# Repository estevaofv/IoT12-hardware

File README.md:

# Status

**Experimental. Do not replicate.**

**You should be present at all times when using this circuit in case something goes wrong.**

# IoT12-hardware
Schematic and PCB files of the IoT12 solder iron temperature controller for T12 tips.

My [Kicad library](https://github.com/atoomnetmarc/ATOOMNETKICAD) is used in this project.

Control Board:\

Power Supply:\

# Checklist

:ballot_box_with_check:Design schematic\
:ballot_box_with_check:Route V1 control board PCB\
:ballot_box_with_check:Slept a few days before ordering V1 control board PCB\
:ballot_box_with_check:Order V1 control board PCB\
:ballot_box_with_check:Made my first github repository\
:ballot_box_with_check:V1 control board PCB arrived\
:ballot_box_with_check:Solder V1 control board PCB and make assembly instructions\
:ballot_box_with_check:Observe that there is something wrong in schematic\
:ballot_box_with_check:Debug V1 control board PCB\
:ballot_box_with_check:Redesign control board PCB, add microcontroller\
:ballot_box_with_check:Order V2 control board PCB\
:ballot_box_with_check:Design power supply PCB\
:ballot_box_with_check:Order power supply PCB\
:ballot_box_with_check:V2 control board PCB and power supply PCB arrived\
:ballot_box_with_check:Solder V2 control board PCB and make assembly instructions\
:ballot_box_with_check:Solder V1 power supply PCB and make assembly instructions\
:black_square_button:Debug V2 control board PCB\
:ballot_box_with_check:Start making firmware\
:black_square_button:Finish first firmware version\
:black_square_button:...\
:black_square_button:profit

# Checklist V2.0 control PCB

Worky (after bodge fix)?

:ballot_box_with_check:SAMD21 debug LED\
:ballot_box_with_check:SAMD21 USB device\
:ballot_box_with_check:SAMD21 SWD\
:ballot_box_with_check:SAMD21 TP1/D0\
:ballot_box_with_check:SAMD21 TP2/D1\
:ballot_box_with_check:SAMD21 TP3/D9\
:ballot_box_with_check:SAMD21 TP4/D10\
:ballot_box_with_check:SAMD21 HEAT_INT\
:ballot_box_with_check:SAMD21 HEAT_PWM\
:ballot_box_with_check:SAMD21 I2C minion\
:ballot_box_with_check:SAMD21 I2S_GAIN0\
:ballot_box_with_check:SAMD21 I2S_GAIN1\
:ballot_box_with_check:SAMD21 I2S_SD\
:ballot_box_with_check:SAMD21 ADC_RDY\
:ballot_box_with_check:SAMD21 I2C ADC\
:ballot_box_with_check:SAMD21 I2C ADC NTC\
:ballot_box_with_check:SAMD21 I2C ADC TEMP\
:ballot_box_with_check:SAMD21 I2C ADC VIN\
:ballot_box_with_check:SAMD21 I2C ADC IRON_CURRENT\
:ballot_box_with_check:SAMD21 I2C EEPROM\
:ballot_box_with_check:SAMD21 ADC NTC\
:ballot_box_with_check:SAMD21 ADC TEMP\
:ballot_box_with_check:SAMD21 ADC VIN\
:ballot_box_with_check:SAMD21 ADC IRON_CURRENT\
:ballot_box_with_check:SAMD21 ADC AIN_COMP\
:ballot_box_with_check:SAMD21 AC AIN_COMP\
:ballot_box_with_check:ESP32 LCD_LED\
:ballot_box_with_check:ESP32 ROT_SW\
:ballot_box_with_check:ESP32 ROT_A\
:ballot_box_with_check:ESP32 ROT_B\
:ballot_box_with_check:ESP32 I2S\
:ballot_box_with_check:ESP32 I2C\
:ballot_box_with_check:ESP32 JTAG\
:ballot_box_with_check:ESP32 LCD\
:ballot_box_with_check:ESP32 HEAT_INT

# Changelog

**Control board PCB version V2.1**

- Swapped SDA/SCL I2C minion pins on heater controller.
- Swapped SDA/SCL I2C master pins on heater controller.
- Renamed PWM_HEAT to HEAT_PWM.
- Re-added MAX809S voltage monitor to keep ESP32 in reset if 3.3V is too low.
- Changed value of R82 from 1M to 4k7.

**Control board PCB version V2.0**

- Replace safety features by microcontroller.
- Heating control now done by microcontroller.
- Changed shape and layout of pcb.

**Control board PCB version V1.1**

- Added explanation to schematic about using matched resistors for the instrumentation amplifiers.
- Changed gain resistors of the instrumentation amplifiers as to keep Vout under 1V at full scale input.
- Added series diode to output of voltage monitor.
- Lowered value of C2-C5 from 10nF to 1nF.
- Added D9 and D10.
- Changed value of R9 from 100R to 1k
- Added circuit to shutdown heating in case of overheating tip.

**Control board PCB version V1.0**

- First version that got made into PCB form.

# Eratta

**Control board PCB version V2.1**

- No known erratum.

**Control board PCB version V2.0**

- I2C to heater controller not working. SDA/SCL are swapped. Swap them on the PCB near R55 and R56 to make the ESP32 communicate to the heater controller.
- A theme is developing :unamused:. I2C from the heater controller to the I2C EEPROM and ADC is not working. SDA/SCL are swapped. Swap them between R53, R54 and the heater controller on the bottom where the SDA/SCL traces run next to each other.
- ESP32 will lockup if power supply rise time is too slow.

**Control board PCB version V1.1**

- Overheating circuit not very stable. No fix.

**Control board PCB version V1.0**

- Silkscreen error in 'Solder iron connector'-block. '5, red, +.' and '4, black, ground.' are switched resulting in negative voltages for positive temperatures. Switch leads will solve this. Corrected in next PCB version.
- Gain of instrumentation amplifiers not correct.
- Programming by USB is impossible.
- Measuring temperature takes too long (20ms).

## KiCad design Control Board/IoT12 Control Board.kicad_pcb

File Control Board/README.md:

# Assembly instructions Control Board

## Solder

Solder components in the following order.
Use the [interactive BOM](bom/ibom.html) for values and positions of the components.

### Integrated circuit

U1.
U2.
U3, U4.
U5.
U6.
U7.

### Transistor

Q1, Q2.
Q3.

### Diode

D1, D2, D3, D4, D12.
D5.
D6, D7, D8.
D9.
D10.
D11.

### Inductor

L1.
L2.

### Resistor

R1.
R10, R11, R12.
R20.
R21.
R30.
R31, R32, R33, R34.
R40.
R52.
R50, R51, R53, R54, R55, R56, R57, R58, R59, R82.
R60, R61, R62, R63. **Read schematic notes about these resistors.**
R64.
R70.
R71, R72.
R80, R81, R83, R84.

### Capacitor

C1, C2.
C10.
C20, C21, C22.
C30, C31, C32, C33, C34, C35, C36, C37, C38.
C40, C41.
C50, C60, C61.
C70, C71, C73.

### Crystal

Y1.

## Clean PCB

[Clean your printed circuit board](http://letmegooglethat.com/?q=how+to+clean+flux+after+soldering). It should be squeaky clean, no flux residue or other crud should remain.

### Switch, back of PCB

SW2.

### Connector, back of PCB

J10.

### Connector, front of PCB

A2: 2 pcs of 1x8pin 2.54mm female headers.

### Connector, back of PCB

A1: 2 pcs of 1x19pin 2.54mm female headers.
J9, J10. 2x5pin 2.54mm male headers.

### Fuse, back of PCB

## Clean PCB, again.

Yes, do it.

### Encoder, front of PCB

Solder SW1 and remove nut and washer.

### Module, front of PCB

A3. Use pin male headers. Also for SPK pins.

## Inspect

Inspect all solder joints. They should all be [nicely soldered](https://www.google.com/search?q=proper+solder+joint), no [solder bridges](https://www.google.com/search?q=picture+of+a+solder+bridge) should be present. Have a magnifying glass or (digital) microscope? Use it.

### GX12-5 connector

Solder some wires between a GX12-5 socket connector and the back of the pcb. On the back of the pcb there are a few pads labeled 1 to 5, solder them to pin 1 to 5 on the GX12-5 connector.

| Pin#  | Wire color    | Description   |
| --:   | --            | --            |
| 1     | blue          | shake         |
| 2     | white         | NTC           |
| 3     | green         | ESD           |
| 4     | black         | T12-          |
| 5     | red           | T12+          |

## Testing

Connect a (KSGER) T12 solder iron handle with the T12 tip firmly seated inside.

- Measure about 1MΩ between the tip of the iron and EARTH hole at the Power supply connection on the PCB.
- Now measure some values at the solder iron connector holes.\
The heater resistor between 4 (black) and 5 (red): 8Ω
- Switch over to measure mV. When you have not touched the handle and tip for half an hour you should read 0mV. Grab the tip with your hand. You should notice an increasing voltage, possibly a rise until 0.1mV. It is possible your voltmeter is not capable of measuring in the microvolt range. You can heat the tip with a flame for a few seconds to increase the voltage some more.
- The NTC between 4 (black) and 2 (white): 5KΩ@22°C, but that could vary slightly when not measuring at the same room temperature.
- Test the tilt sensor. Point iron up and measure between 1 (blue) and 3 (green): >2MΩ\
Point iron down and measure a low resistance: <100Ω

Solder a red wire to 24V and black wire to GND of the power supply connector holes, both on the back.\
Slowly increase power supply until 10V with max 50mA power. Measure voltage at C71. You should measure 5V. The current draw should be under 10mA.

Switch off power supply and mount the LCD display module and the ESP32 module.

Increase maximum power supply current to 250mA. Instantly increase voltage to 5V, the slowly to 10V, current should not exceed 150mA. When at 10V the current draw should be under 100mA.
You may increase voltage to 24V, consumed power should be under 40mA.

When all tests went well, start writing your own firmware. Or [flash my firmware](https://github.com/atoomnetmarc/IoT12-firmware) when it becomes available.\
Projected firmware availability date: soon™

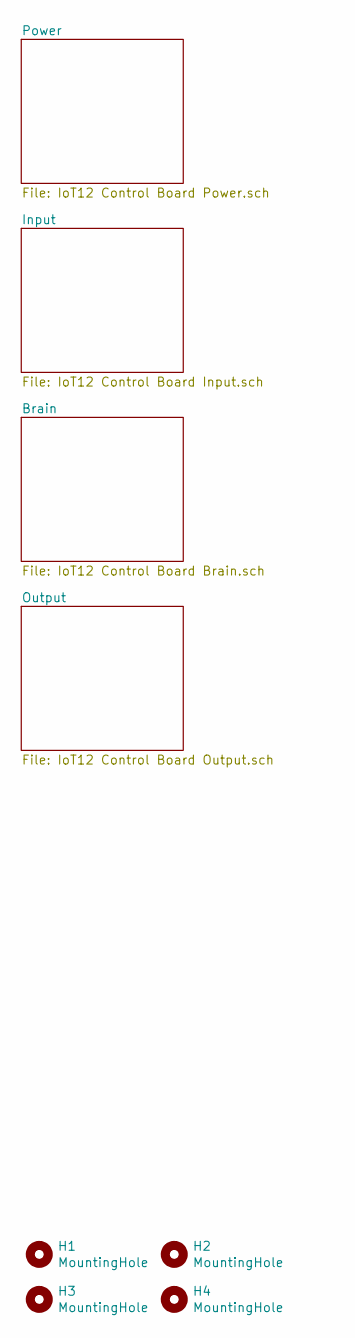
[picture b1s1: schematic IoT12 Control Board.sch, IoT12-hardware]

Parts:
H1, H2, H3, H4: MountingHole; MountingHole_3.2mm_M3_Pad_Via

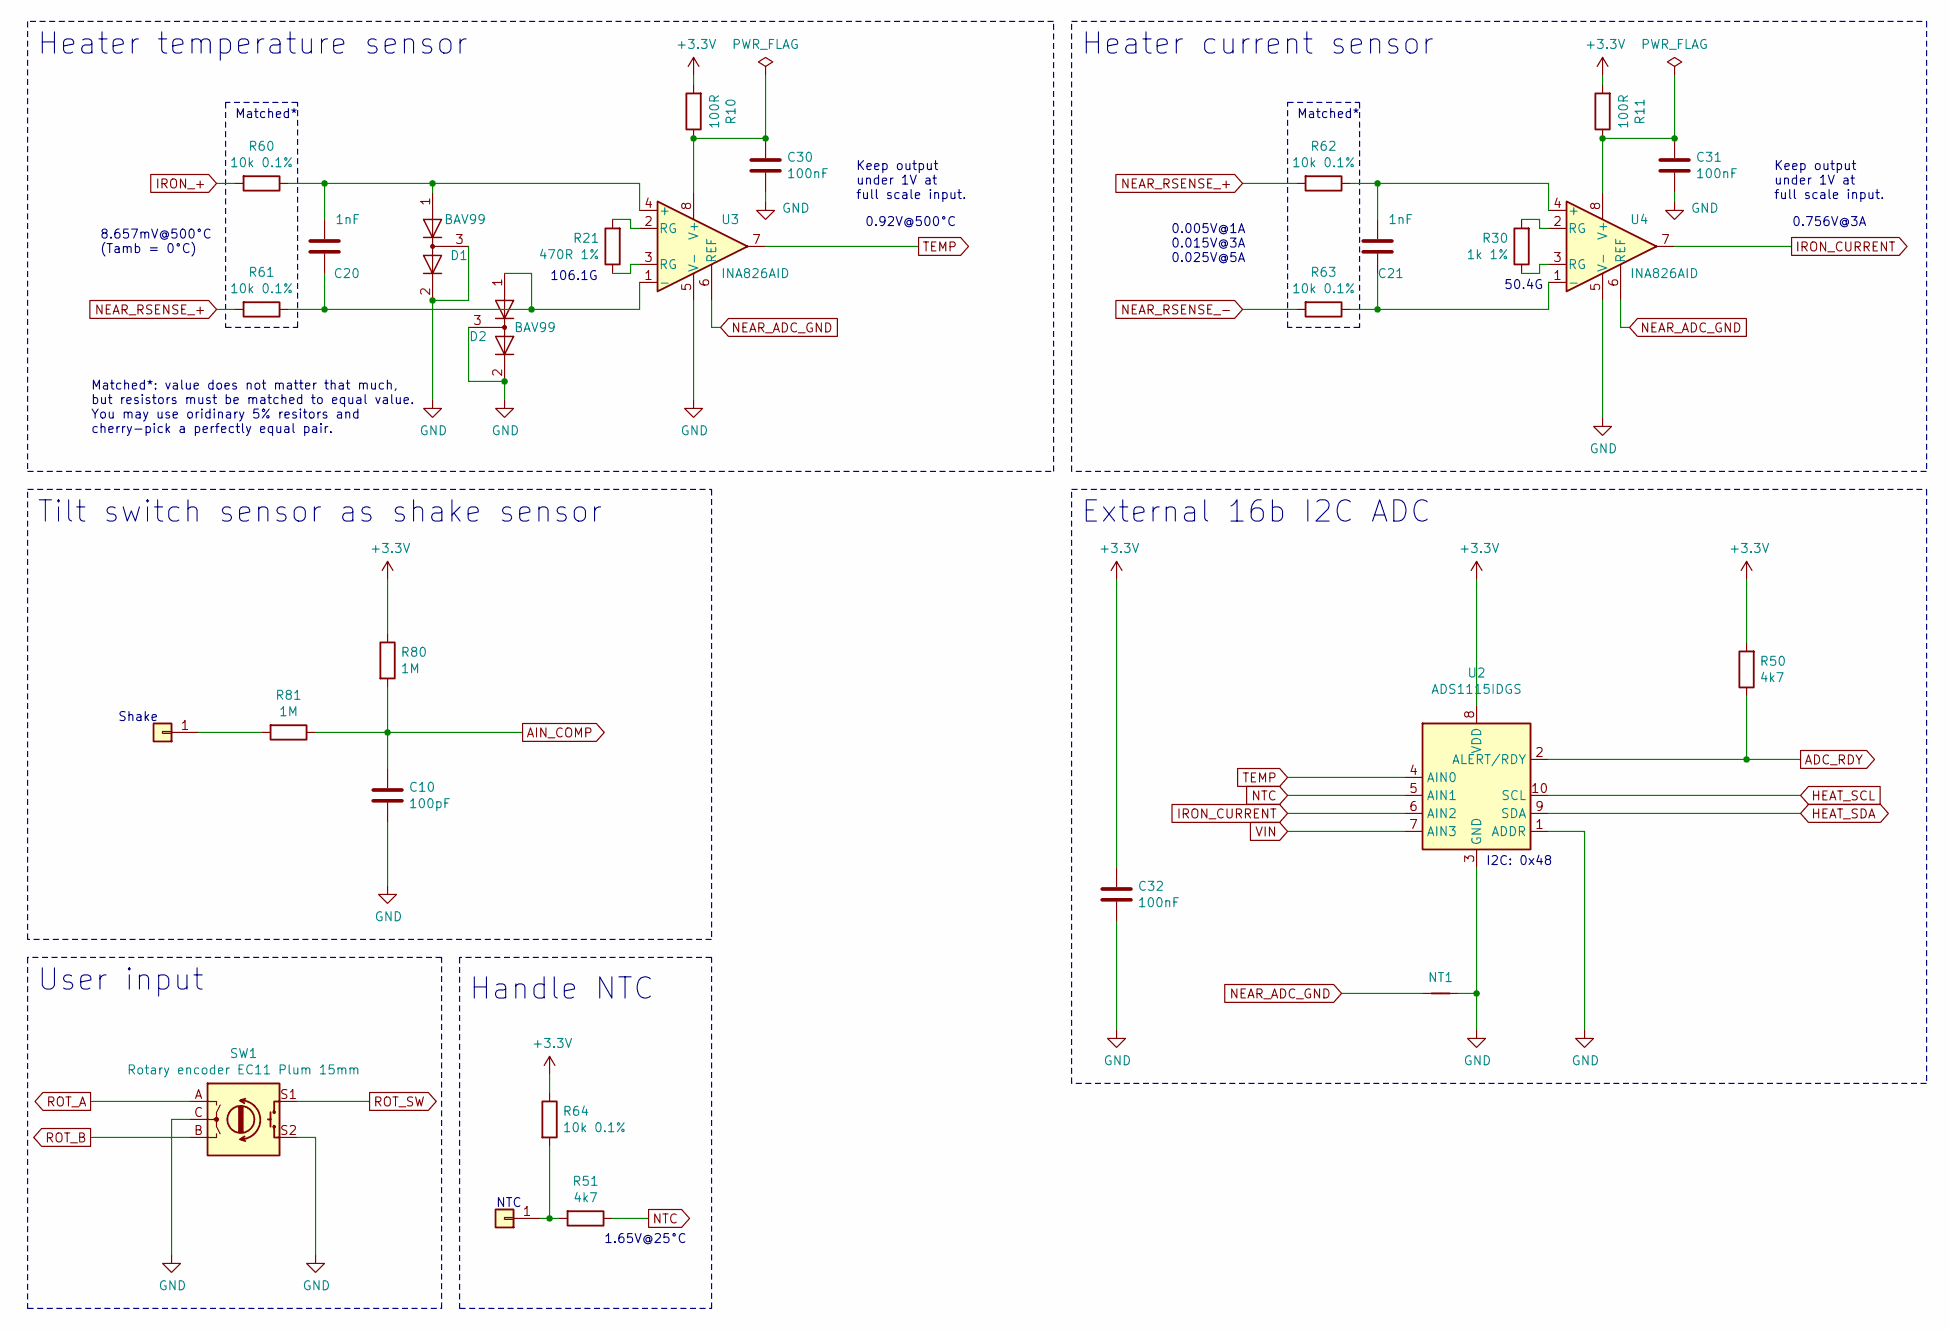
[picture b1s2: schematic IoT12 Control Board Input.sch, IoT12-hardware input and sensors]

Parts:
C10: 100pF; C_0805_2012Metric_Pad1.18x1.45mm_HandSolder
C20, C21: 1nF; C_0805_2012Metric_Pad1.18x1.45mm_HandSolder
C30, C31, C32: 100nF; C_0805_2012Metric_Pad1.18x1.45mm_HandSolder
D1, D2: BAV99; SOT-23
J1, J2: TestPoint_THTPad_D2.0mm_Drill1.0mm
NT1: NetTie-2_SMD_Pad0.25mm
R10, R11: 100R; R_0805_2012Metric_Pad1.20x1.40mm_HandSolder
R21: 470R 1%; R_0805_2012Metric_Pad1.20x1.40mm_HandSolder
R30: 1k 1%; R_0805_2012Metric_Pad1.20x1.40mm_HandSolder
R50, R51: 4k7; R_0805_2012Metric_Pad1.20x1.40mm_HandSolder
R60, R61, R62, R63, R64: 10k 0.1%; R_0805_2012Metric_Pad1.20x1.40mm_HandSolder
R80, R81: 1M; R_0805_2012Metric_Pad1.20x1.40mm_HandSolder
SW1: Rotary encoder EC11 Plum 15mm; RotaryEncoder_Alps_EC11E-Switch_Vertical_H20mm_CircularMoun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
U2: ADS1115IDGS; TSSOP-10_3x3mm_P0.5mm
U3, U4: INA826AID; SOIC-8_3.9x4.9mm_P1.27mm

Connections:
ADC_RDY: R50.1, U2.2 (ALERT/RDY); also elsewhere on the board
AIN_COMP: C10.1, R80.2, R81.1; also elsewhere on the board
GND: C10.2, C30.2, C31.2, C32.2, D1.2 (A), D1.3 (K), D2.2 (A), D2.3 (K), NT1.2, SW1.C, SW1.S2, U2.1 (ADDR), U2.3 (GND), U3.5 (V-), U4.5 (V-); also elsewhere on the board
HEAT_SCL: U2.10 (SCL); also elsewhere on the board
HEAT_SDA: U2.9 (SDA); also elsewhere on the board
IRON_+: R60.2; also elsewhere on the board
IRON_CURRENT: U2.6 (AIN2), U4.7; also elsewhere on the board
NEAR_ADC_GND: NT1.1, U3.6 (REF), U4.6 (REF)
NEAR_RSENSE_+: R61.2, R62.2; also elsewhere on the board
NEAR_RSENSE_-: R63.2; also elsewhere on the board
NTC: R51.1, U2.5 (AIN1); also elsewhere on the board
unnamed: C20.1, D1.1 (K), R60.1, U3.4 (+)
unnamed: C20.2, D2.1 (K), R61.1, U3.1 (-)
unnamed: C21.1, R62.1, U4.4 (+)
unnamed: C21.2, R63.1, U4.1 (-)
unnamed: C30.1, R10.1, U3.8 (V+)
unnamed: C31.1, R11.1, U4.8 (V+)
unnamed: J1.1, R81.2
unnamed: J2.1, R51.2, R64.2
unnamed: R21.1, U3.3 (RG)
unnamed: R21.2, U3.2 (RG)
unnamed: R30.1, U4.3 (RG)
unnamed: R30.2, U4.2 (RG)
ROT_A: SW1.A; also elsewhere on the board
ROT_SW: SW1.S1; also elsewhere on the board
TEMP: U2.4 (AIN0), U3.7; also elsewhere on the board
VIN: U2.7 (AIN3); also elsewhere on the board

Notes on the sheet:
User input
Heater temperature sensor
Heater current sensor
Handle NTC
NTC
Shake
Tilt switch sensor as shake sensor
50.4G
Matched*
0.005V@1A 0.015V@3A 0.025V@5A
106.1G
8.657mV@500°C (Tamb = 0°C)
0.92V@500°C
1.65V@25°C
Matched*: value does not matter that much, but resistors must be matched to equal value. You may use oridinary 5% resitors and cherry-pick a perfectly equal pair.
Keep output under 1V at full scale input.
0.756V@3A
External 16b I2C ADC
I2C: 0x48

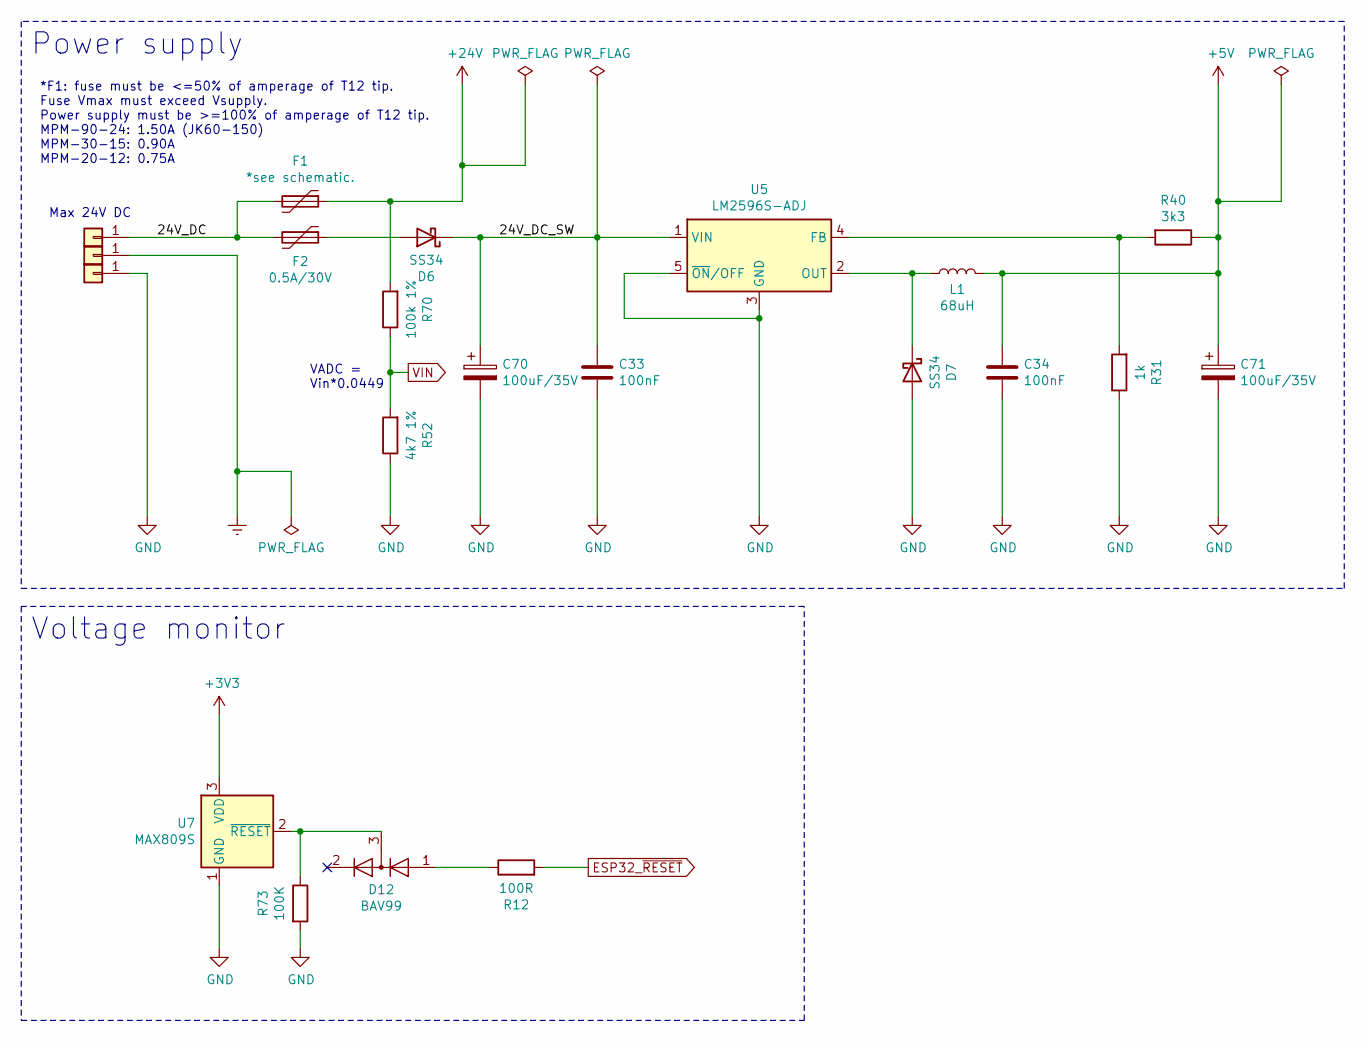
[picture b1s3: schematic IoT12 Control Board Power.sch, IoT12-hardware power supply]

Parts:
C33, C34: 100nF; C_0805_2012Metric_Pad1.18x1.45mm_HandSolder
C70, C71: 100uF/35V; CP_Elec_6.3x7.7
D6, D7: SS34; D_SMA
D12: BAV99; SOT-23
F1: *see schematic.; Fuse_Bourns_MF-RG1000
F2: 0.5A/30V; Fuse_Bourns_MF-RG400
J6, J7, J8: TestPoint_THTPad_D2.0mm_Drill1.0mm
L1: 68uH; L_12x12mm_H8mm
R12: 100R; R_0805_2012Metric_Pad1.20x1.40mm_HandSolder
R31: 1k; R_0805_2012Metric_Pad1.20x1.40mm_HandSolder
R40: 3k3; R_0805_2012Metric_Pad1.20x1.40mm_HandSolder
R52: 4k7 1%; R_0805_2012Metric_Pad1.20x1.40mm_HandSolder
R70: 100k 1%; R_0805_2012Metric_Pad1.20x1.40mm_HandSolder
R73: 100K; R_0805_2012Metric_Pad1.20x1.40mm_HandSolder
U5: LM2596S-ADJ; TO-263-5_TabPin3
U7: MAX809S; SOT-23

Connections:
+5V: C34.1, C71.1, L1.2, R40.1; also elsewhere on the board
+24V: F1.1, R70.2; also elsewhere on the board
/Power/24V_DC: F1.2, F2.2, J6.1
/Power/24V_DC_SW: C33.1, C70.1, D6.1 (K), U5.1 (VIN)
ESP32_~RESET: R12.2; also elsewhere on the board
Earth: J7.1; also elsewhere on the board
GND: C33.2, C34.2, C70.2, C71.2, D7.2 (A), J8.1, R31.1, R52.1, R73.2, U5.3 (GND), U5.5 (~ON~/OFF), U7.1 (GND); also elsewhere on the board
unnamed: D6.2 (A), F2.1
unnamed: D7.1 (K), L1.1, U5.2 (OUT)
unnamed: D12.1 (K), R12.1
unnamed: D12.3 (K), R73.1, U7.2 (~RESET)
unnamed: R31.2, R40.2, U5.4 (FB)
VIN: R52.2, R70.1; also elsewhere on the board

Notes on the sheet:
Power supply
VADC = Vin*0.0449
Max 24V DC
Voltage monitor
*F1: fuse must be <=50% of amperage of T12 tip. Fuse Vmax must exceed Vsupply. Power supply must be >=100% of amperage of T12 tip. MPM-90-24: 1.50A (JK60-150) MPM-30-15: 0.90A MPM-20-12: 0.75A

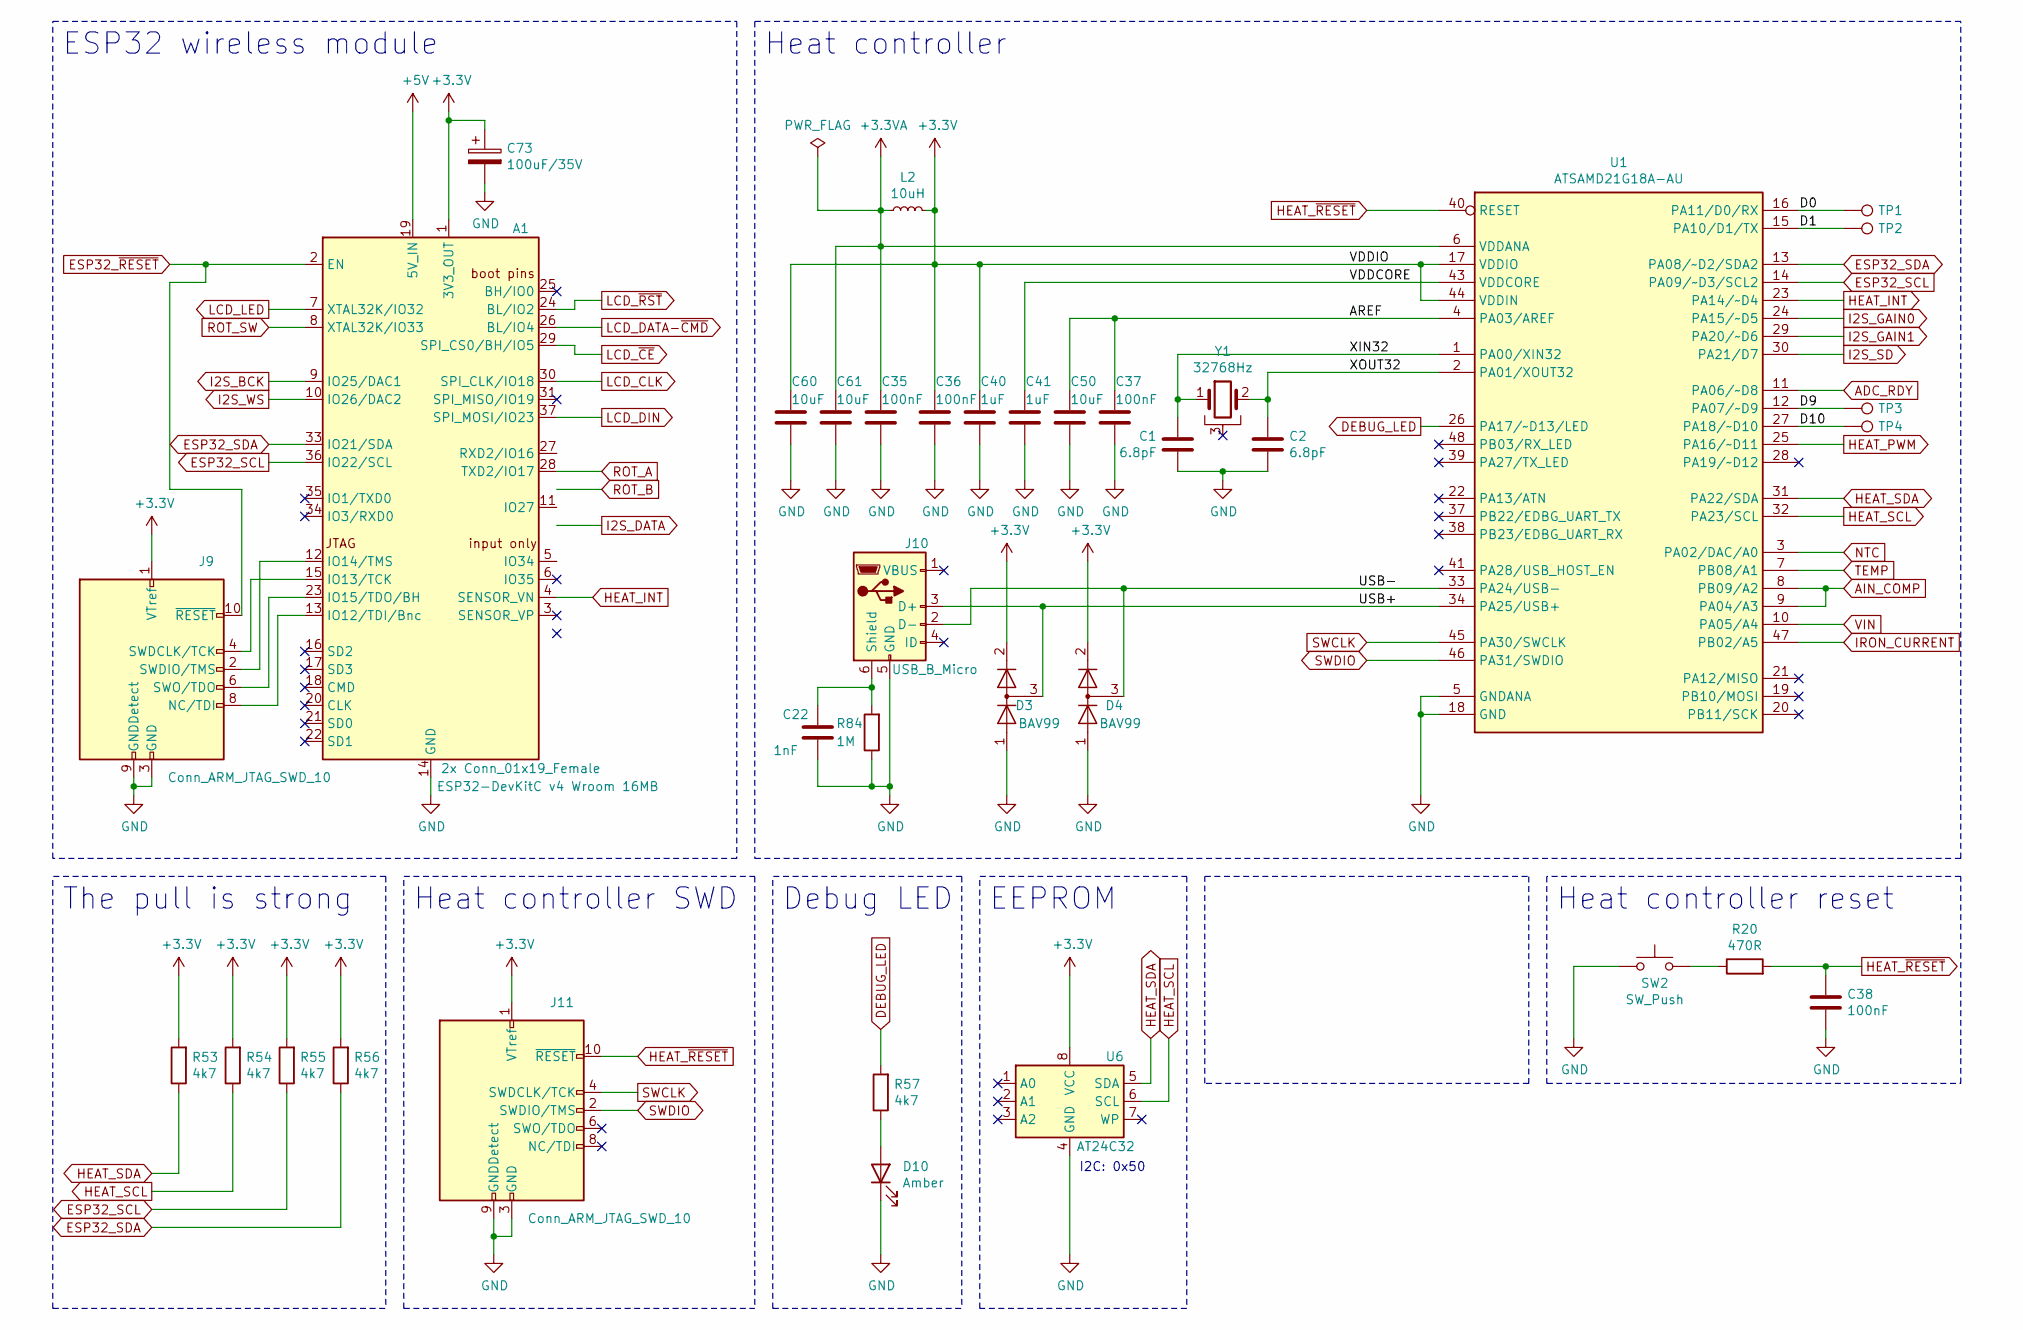
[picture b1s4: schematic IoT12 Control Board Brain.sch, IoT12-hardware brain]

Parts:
A1: 2x Conn_01x19_Female; ESP32-DevKitC
C1, C2: 6.8pF; C_0805_2012Metric_Pad1.18x1.45mm_HandSolder
C22: 1nF; C_0805_2012Metric_Pad1.18x1.45mm_HandSolder
C35, C36, C37, C38: 100nF; C_0805_2012Metric_Pad1.18x1.45mm_HandSolder
C40, C41: 1uF; C_0805_2012Metric_Pad1.18x1.45mm_HandSolder
C50, C60, C61: 10uF; C_0805_2012Metric_Pad1.18x1.45mm_HandSolder
C73: 100uF/35V; CP_Elec_6.3x7.7
D3, D4: BAV99; SOT-23
D10: Amber; LED_0805_2012Metric_Pad1.15x1.40mm_HandSolder
J9, J11: Conn_ARM_JTAG_SWD_10; PinHeader_2x05_P2.54mm_Vertical
J10: USB_B_Micro; USB_Micro-B_Amphenol_10118194_Horizontal
L2: 10uH; L_0805_2012Metric_Pad1.15x1.40mm_HandSolder
R20: 470R; R_0805_2012Metric_Pad1.20x1.40mm_HandSolder
R53, R54, R55, R56, R57: 4k7; R_0805_2012Metric_Pad1.20x1.40mm_HandSolder
R84: 1M; R_0805_2012Metric_Pad1.20x1.40mm_HandSolder
SW2: SW_Push; SW_SPST_CK_RS282G05A3
TP1, TP2, TP3, TP4: TestPoint; TestPoint_Pad_D0.75mm
U1: ATSAMD21G18A-AU; TQFP-48_7x7mm_P0.5mm
U6: AT24C32; SOIC-8_3.9x4.9mm_P1.27mm
Y1: 32768Hz; Crystal_C26-LF_D2.1mm_L6.5mm_Horizontal_1EP_style1

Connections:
+3.3VA: C35.1, C61.1, L2.1, U1.6 (VDDANA)
+5V: A1.19 (5V_IN); also elsewhere on the board
/Brain/AREF: C37.1, C50.1, U1.4 (PA03/AREF)
/Brain/D0: TP1.1, U1.16 (PA11/D0/RX)
/Brain/D1: TP2.1, U1.15 (PA10/D1/TX)
/Brain/D9: TP3.1, U1.12 (PA07/~~D9)
/Brain/D10: TP4.1, U1.27 (PA18/~~D10)
/Brain/USB+: D3.3 (K), J10.3 (D+), U1.34 (PA25/USB+)
/Brain/USB-: D4.3 (K), J10.2 (D-), U1.33 (PA24/USB-)
/Brain/VDDCORE: C41.1, U1.43 (VDDCORE)
/Brain/XIN32: C1.1, U1.1 (PA00/XIN32), Y1.1
/Brain/XOUT32: C2.1, U1.2 (PA01/XOUT32), Y1.2
ADC_RDY: U1.11 (PA06/~~D8); also elsewhere on the board
AIN_COMP: U1.8 (PB09/A2), U1.9 (PA04/A3); also elsewhere on the board
DEBUG_LED: R57.2, U1.26 (PA17/~~D13/LED)
ESP32_SCL: A1.36 (IO22/SCL), R55.1, U1.14 (PA09/~~D3/SCL2)
ESP32_SDA: A1.33 (IO21/SDA), R56.1, U1.13 (PA08/~~D2/SDA2)
ESP32_~RESET: A1.2 (EN), J9.10 (~RESET~); also elsewhere on the board
GND: A1.14 (GND), A1.32 (GND), A1.38 (GND), C1.2, C2.2, C22.2, C35.2, C36.2, C37.2, C38.2, C40.2, C41.2, C50.2, C60.2, C61.2, C73.2, D3.1 (K), D4.1 (K), D10.1 (K), J9.3 (GND), J9.5 (GND), J9.9 (GNDDetect), J10.5 (GND), J11.3 (GND), J11.5 (GND), J11.9 (GNDDetect), R84.1, SW2.1, U1.5 (GNDANA), U1.18 (GND), U1.35 (GND), U1.42 (GND), U6.4 (GND); also elsewhere on the board
HEAT_PWM: U1.25 (PA16/~~D11); also elsewhere on the board
HEAT_SCL: R54.1, U1.32 (PA23/SCL), U6.6 (SCL); also elsewhere on the board
HEAT_SDA: R53.1, U1.31 (PA22/SDA), U6.5 (SDA); also elsewhere on the board
HEAT_~RESET: C38.1, J11.10 (~RESET~), R20.2, U1.40 (RESET)
I2S_BCK: A1.9 (IO25/DAC1); also elsewhere on the board
I2S_DATA: A1.11 (IO27); also elsewhere on the board
I2S_GAIN0: U1.24 (PA15/~~D5); also elsewhere on the board
I2S_GAIN1: U1.29 (PA20/~~D6); also elsewhere on the board
I2S_SD: U1.30 (PA21/D7); also elsewhere on the board
I2S_WS: A1.10 (IO26/DAC2); also elsewhere on the board
IRON_CURRENT: U1.47 (PB02/A5); also elsewhere on the board
LCD_CLK: A1.30 (SPI_CLK/IO18); also elsewhere on the board
LCD_DATA-~CMD: A1.26 (BL/IO4); also elsewhere on the board
LCD_DIN: A1.37 (SPI_MOSI/IO23); also elsewhere on the board
LCD_LED: A1.7 (XTAL32K/IO32); also elsewhere on the board
LCD_~CE: A1.29 (SPI_CS0/BH/IO5); also elsewhere on the board
LCD_~RST: A1.24 (BL/IO2); also elsewhere on the board
NTC: U1.3 (PA02/DAC/A0); also elsewhere on the board
unnamed: A1.12 (IO14/TMS), J9.2 (SWDIO/TMS)
unnamed: A1.13 (IO12/TDI/Bnc), J9.8 (NC/TDI)
unnamed: A1.15 (IO13/TCK), J9.4 (SWDCLK/TCK)
unnamed: A1.23 (IO15/TDO/BH), J9.6 (SWO/TDO)
unnamed: C22.1, J10.6 (Shield), R84.2
unnamed: D10.2 (A), R57.1
unnamed: R20.1, SW2.2
ROT_A: A1.27 (RXD2/IO16); also elsewhere on the board
ROT_SW: A1.8 (XTAL32K/IO33); also elsewhere on the board
SWCLK: J11.4 (SWDCLK/TCK), U1.45 (PA30/SWCLK)
SWDIO: J11.2 (SWDIO/TMS), U1.46 (PA31/SWDIO)
TEMP: U1.7 (PB08/A1); also elsewhere on the board
VIN: U1.10 (PA05/A4); also elsewhere on the board

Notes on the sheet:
ESP32 wireless module
Heat controller
Heat controller SWD
Heat controller reset
Debug LED
The pull is strong
EEPROM
I2C: 0x50

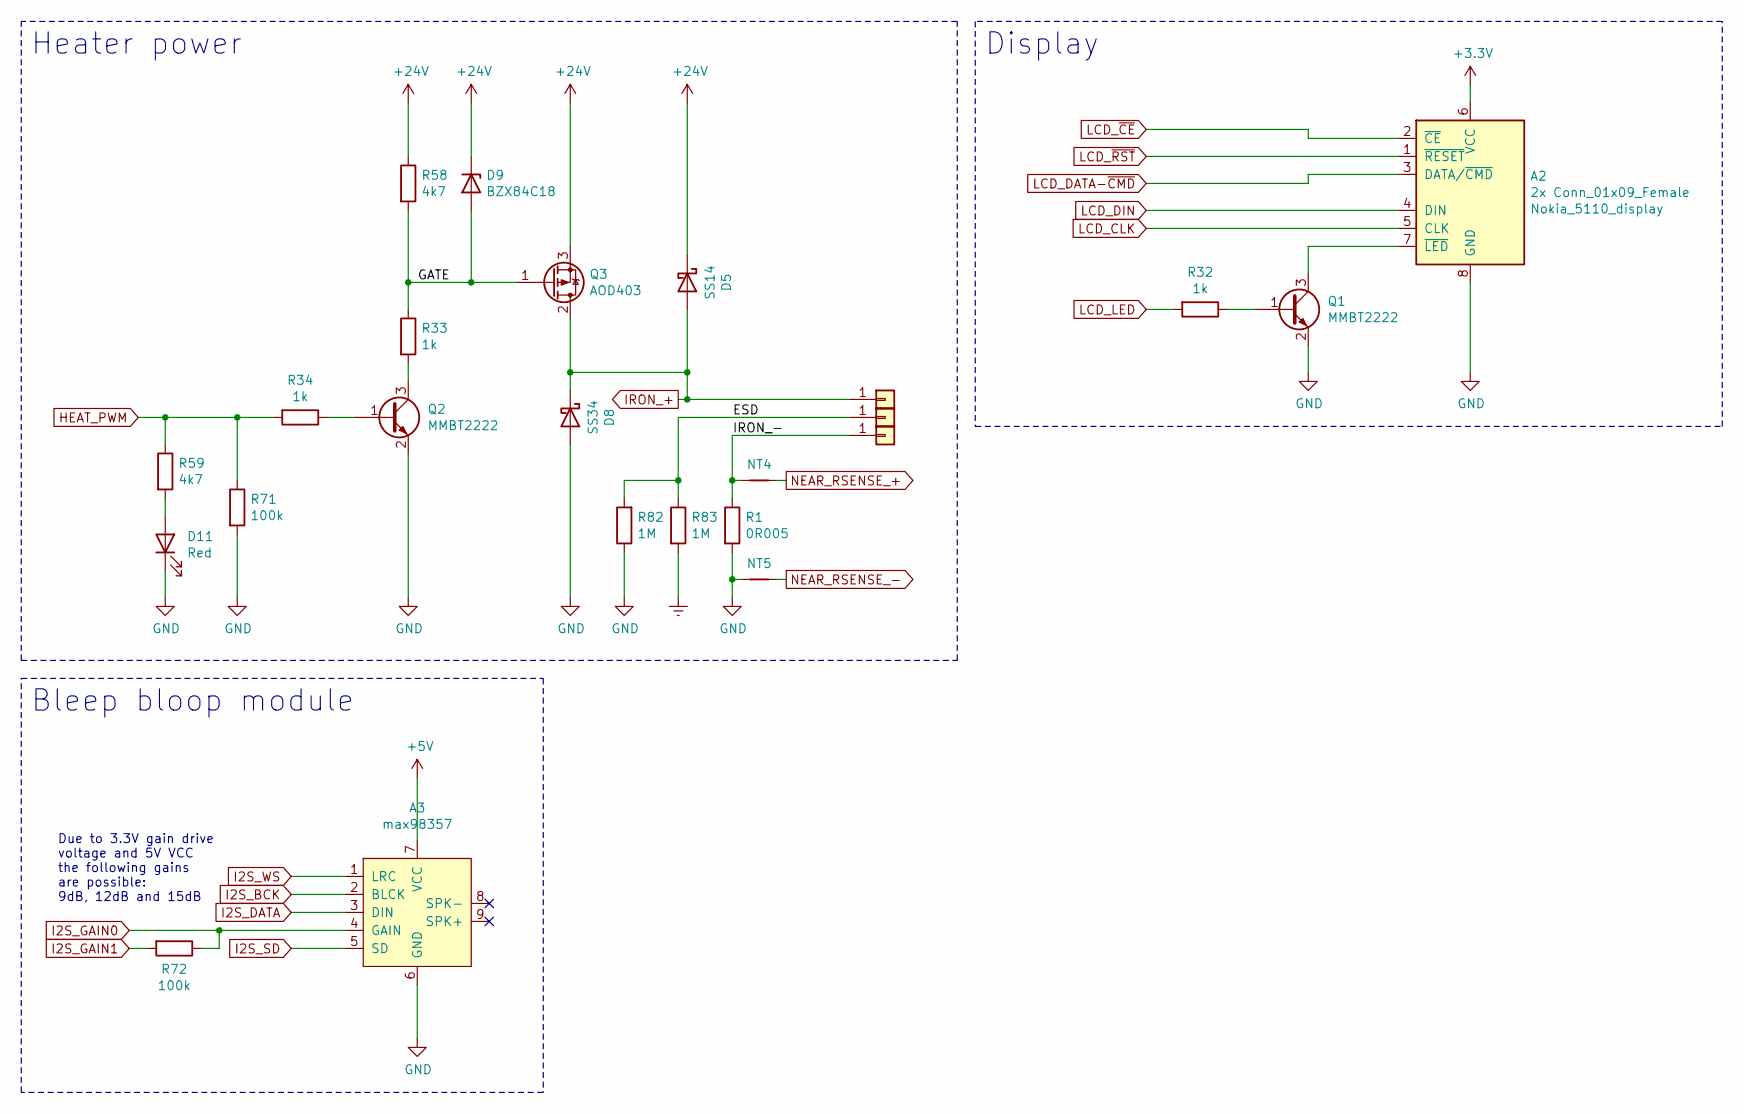
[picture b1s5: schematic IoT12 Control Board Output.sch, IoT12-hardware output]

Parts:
A2: 2x Conn_01x09_Female; Nokia_5110_display_module
A3: max98357
D5: SS14; D_SMA
D8: SS34; D_SMA
D9: BZX84C18; D_SOT-23_ANK
D11: Red; LED_0805_2012Metric_Pad1.15x1.40mm_HandSolder
J3, J4, J5: TestPoint_THTPad_D2.0mm_Drill1.0mm
NT4, NT5: NetTie-2_SMD_Pad0.25mm
Q1, Q2: MMBT2222; SOT-23
Q3: AOD403; TO-252-2
R1: 0R005; R_2512_6332Metric_Pad1.52x3.35mm_HandSolder
R32, R33, R34: 1k; R_0805_2012Metric_Pad1.20x1.40mm_HandSolder
R58, R59: 4k7; R_0805_2012Metric_Pad1.20x1.40mm_HandSolder
R71, R72: 100k; R_0805_2012Metric_Pad1.20x1.40mm_HandSolder
R82, R83: 1M; R_0805_2012Metric_Pad1.20x1.40mm_HandSolder

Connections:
+5V: A3.7 (VCC); also elsewhere on the board
+24V: D5.1 (K), D9.1 (K), Q3.3 (S), R58.1; also elsewhere on the board
/Output/ESD: J3.1, R82.2, R83.1
/Output/GATE: D9.2 (A), Q3.1 (G), R33.1, R58.2
/Output/IRON_-: J4.1, NT4.1, R1.1
Earth: R83.2; also elsewhere on the board
GND: A2.8 (GND), A3.6 (GND), D8.2 (A), D11.1 (K), NT5.1, Q1.2 (E), Q2.2 (E), R1.2, R71.2, R82.1; also elsewhere on the board
HEAT_PWM: R34.2, R59.1, R71.1; also elsewhere on the board
I2S_BCK: A3.2 (BLCK); also elsewhere on the board
I2S_DATA: A3.3 (DIN); also elsewhere on the board
I2S_GAIN0: A3.4 (GAIN), R72.1; also elsewhere on the board
I2S_GAIN1: R72.2; also elsewhere on the board
I2S_SD: A3.5 (SD); also elsewhere on the board
I2S_WS: A3.1 (LRC); also elsewhere on the board
IRON_+: D5.2 (A), D8.1 (K), J5.1, Q3.2 (D); also elsewhere on the board
LCD_CLK: A2.5 (CLK); also elsewhere on the board
LCD_DATA-~CMD: A2.3 (DATA/~CMD); also elsewhere on the board
LCD_DIN: A2.4 (DIN); also elsewhere on the board
LCD_LED: R32.2; also elsewhere on the board
LCD_~CE: A2.2 (~CE); also elsewhere on the board
LCD_~RST: A2.1 (~RESET); also elsewhere on the board
NEAR_RSENSE_+: NT4.2; also elsewhere on the board
NEAR_RSENSE_-: NT5.2; also elsewhere on the board
unnamed: A2.7 (~LED), Q1.3 (C)
unnamed: D11.2 (A), R59.2
unnamed: Q1.1 (B), R32.1
unnamed: Q2.1 (B), R34.1
unnamed: Q2.3 (C), R33.2

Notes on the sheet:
Display
Heater power
Bleep bloop module
Due to 3.3V gain drive voltage and 5V VCC the following gains are possible: 9dB, 12dB and 15dB

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
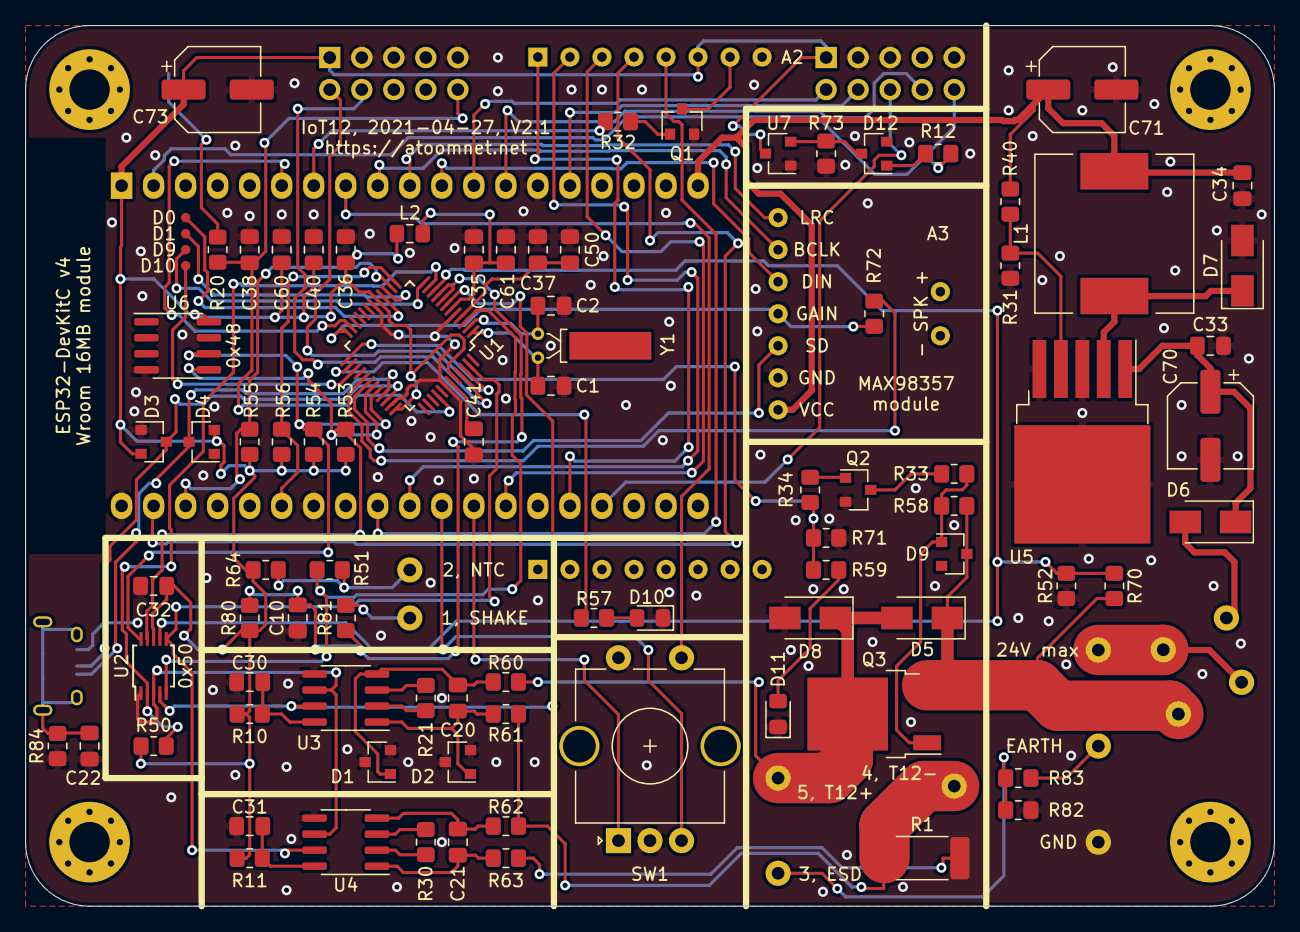
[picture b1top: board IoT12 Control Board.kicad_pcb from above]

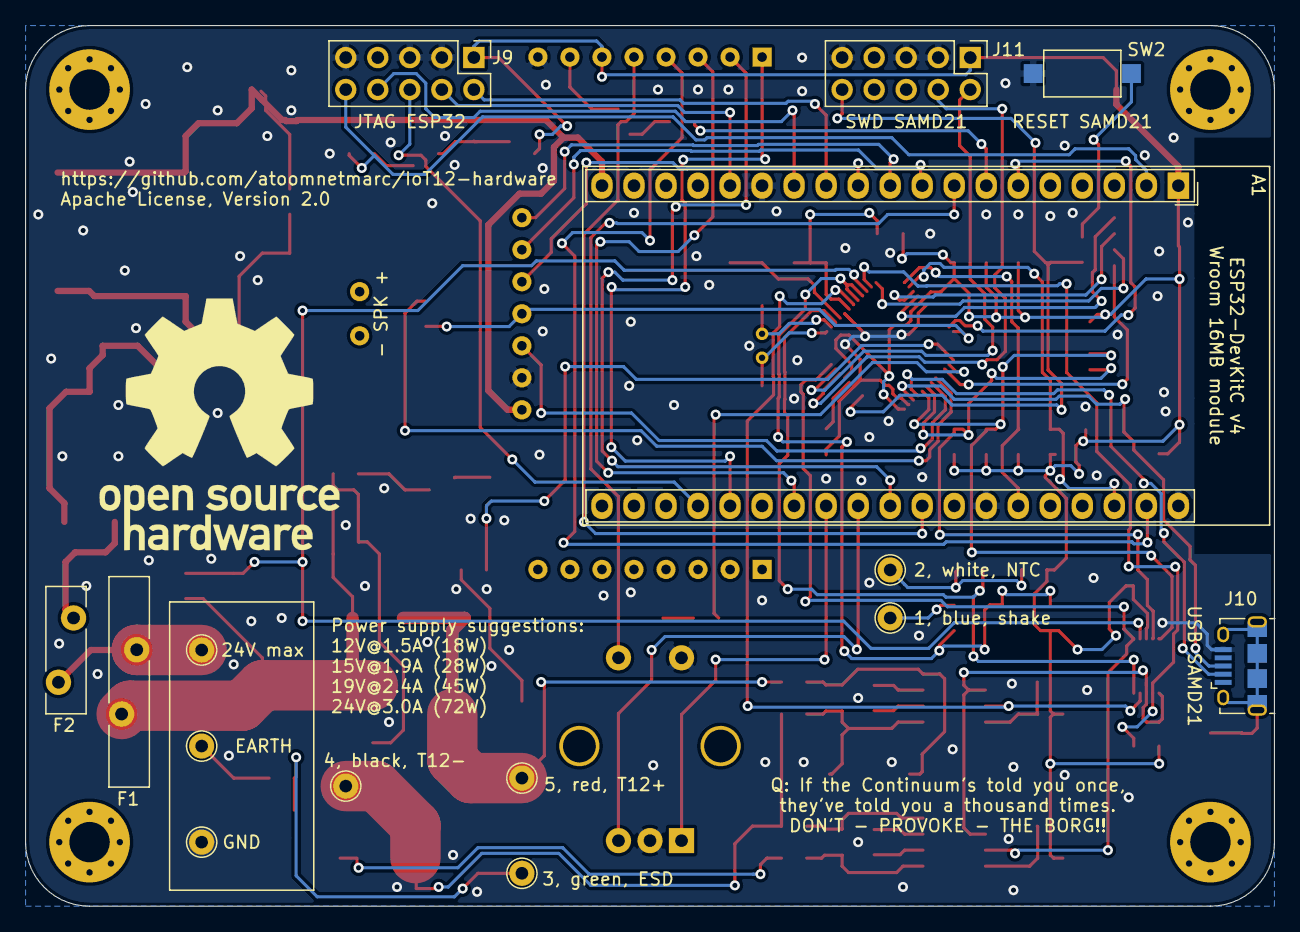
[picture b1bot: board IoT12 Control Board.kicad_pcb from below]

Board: 2 copper layers, 99.1 x 69.8 mm, 113 parts (15 on the bottom side), 86 nets.

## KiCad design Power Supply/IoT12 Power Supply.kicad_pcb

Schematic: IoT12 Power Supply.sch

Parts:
D2: Green; LED_0805_2012Metric_Pad1.15x1.40mm_HandSolder
H1, H2, H3, H4: MountingHole; MountingHole_3.2mm_M3_Pad_Via
J1, J2: Screw_Terminal_01x03; TerminalBlock_bornier-3_P5.08mm
PS1: MPM-90-24; Converter_ACDC_MeanWell_MPM-90-xx_THT
PS2: MPM-30-15*; Converter_ACDC_MeanWell_MPM-30-xx_THT
PS3: MPM-20-12*; Converter_ACDC_MeanWell_MPM-20-xx_THT
R2: 4K7; R_0805_2012Metric_Pad1.20x1.40mm_HandSolder

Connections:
/L: J1.3, PS1.1, PS2.1, PS3.1
/N: J1.2, PS1.2, PS2.2, PS3.2
/Vout+: J2.3, PS1.3, PS2.3, PS3.3, R2.1
/Vout-: D2.1 (K), J2.2, PS1.4, PS2.4, PS3.4
Earth: J1.1, J2.1
unnamed: D2.2 (A), R2.2

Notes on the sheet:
Lower power alternatives

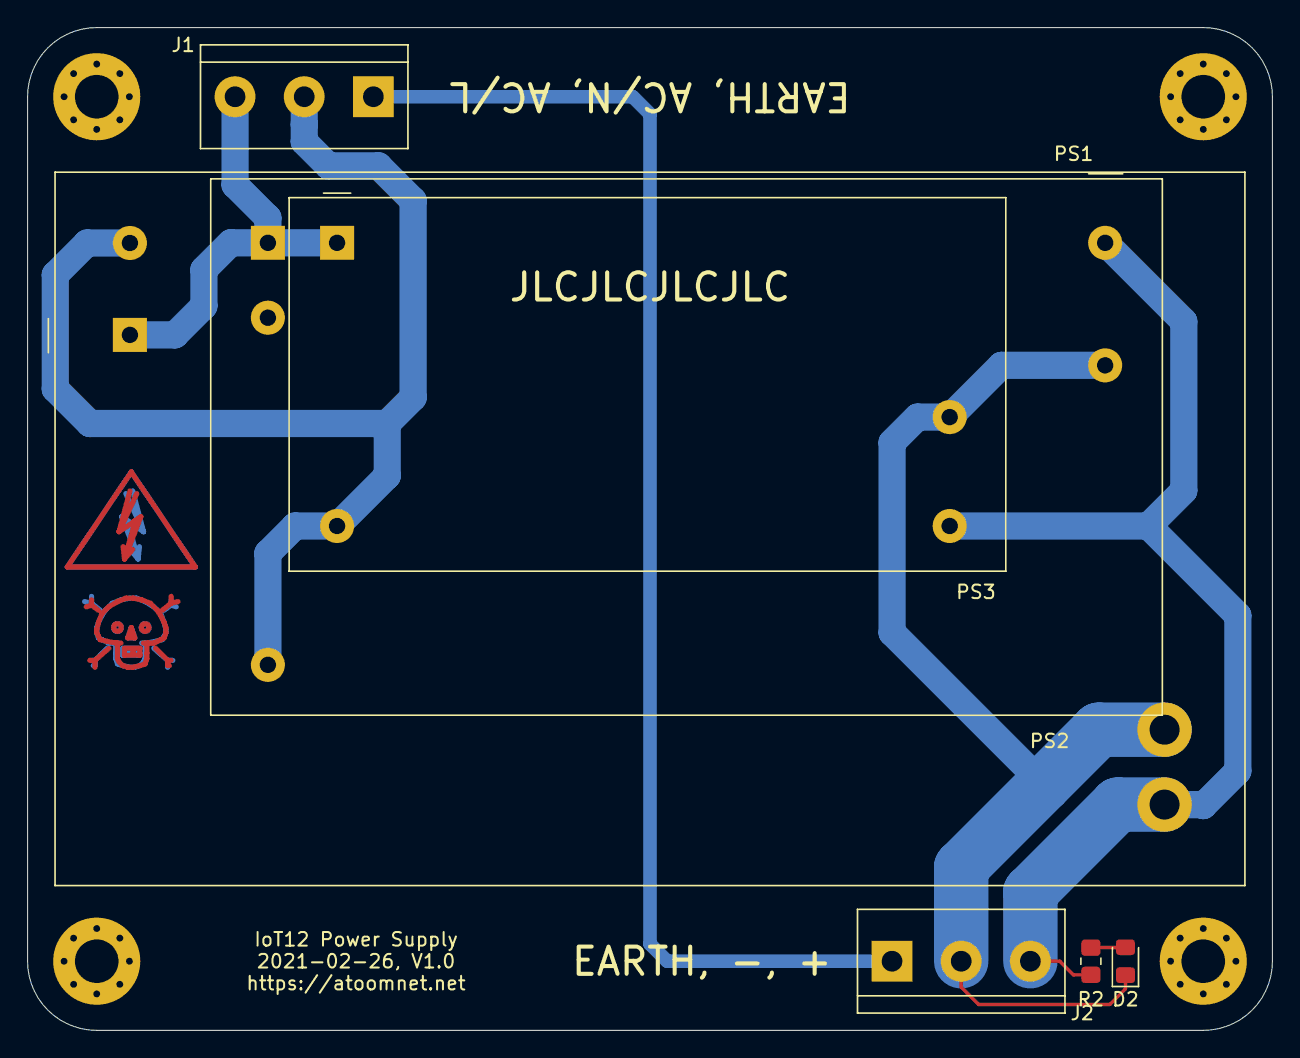
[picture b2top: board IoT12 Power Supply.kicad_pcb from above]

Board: 2 copper layers, 91.4 x 73.7 mm, 11 parts (0 on the bottom side), 6 nets.

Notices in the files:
Control Board/IoT12 Control Board.kicad_pcb:
Apache License, Version 2.0
README.md:
License: Apache 2.0
